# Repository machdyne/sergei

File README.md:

# Sergei Motherboard

Sergei is a motherboard that when paired with a [Sechzig](https://github.com/machdyne/sechzig) compute module can function as a computer.

This repo contains schematics, PCB layouts, pinouts, documentation and a 3D-printable case.

Find more information on the [Sergei product page](https://machdyne.com/product/sergei-motherboard/).

## Using Sergei

Sergei requires a Sechzig module to power on. **When inserting a Sechzig module, make sure that pin 2 on Sergei and pin 2 on the module are both on the same side.**

## Firmware

Sergei has a JTAG and USB CDC interface that are both accessible on the USB-C port. These interfaces are provided by a [fork of pico-dirtyJtag](https://github.com/machdyne/sergei/tree/main/firmware). You can update the RP2040 firmware by holding down the BOOT button and then applying power.

To build the firmware from source:

```
$ cd firmware/pico-dirtyJtag
$ mkdir build
$ cmake ..
$ make
```

## Programming

Program the configuration SRAM of a Sechzig module:

```
sudo openFPGALoader -c dirtyJtag image.bit
```

Program the configuration flash on a Sechzig MLx module:

```
sudo openFPGALoader -f -c dirtyJtag image.bit
```

Program the configuration flash on a Sechzig MX1 module:

```
sudo openFPGALoader -c dirtyJtag -f image.bit --fpga-part xc7a35tftg256
```

## Linux

See the [Kakao Linux](https://github.com/machdyne/kakao) repo for the latest instructions.

## Pinouts

### DDMI Port

See the [DDMI repo](https://github.com/machdyne/ddmi) for details.

## Revisions

| Revision | Stackup | Notes |
| -------- | ------- | ----- |
| V0 | JLC04161H-3313 | Initial production version |

## License

The contents of this repo are released under the [Lone Dynamics Open License](LICENSE.md) with the following exception(s):

  * The pico-dirtyJtag firmware is released under the MIT license; see the firmware LICENSE file for details.

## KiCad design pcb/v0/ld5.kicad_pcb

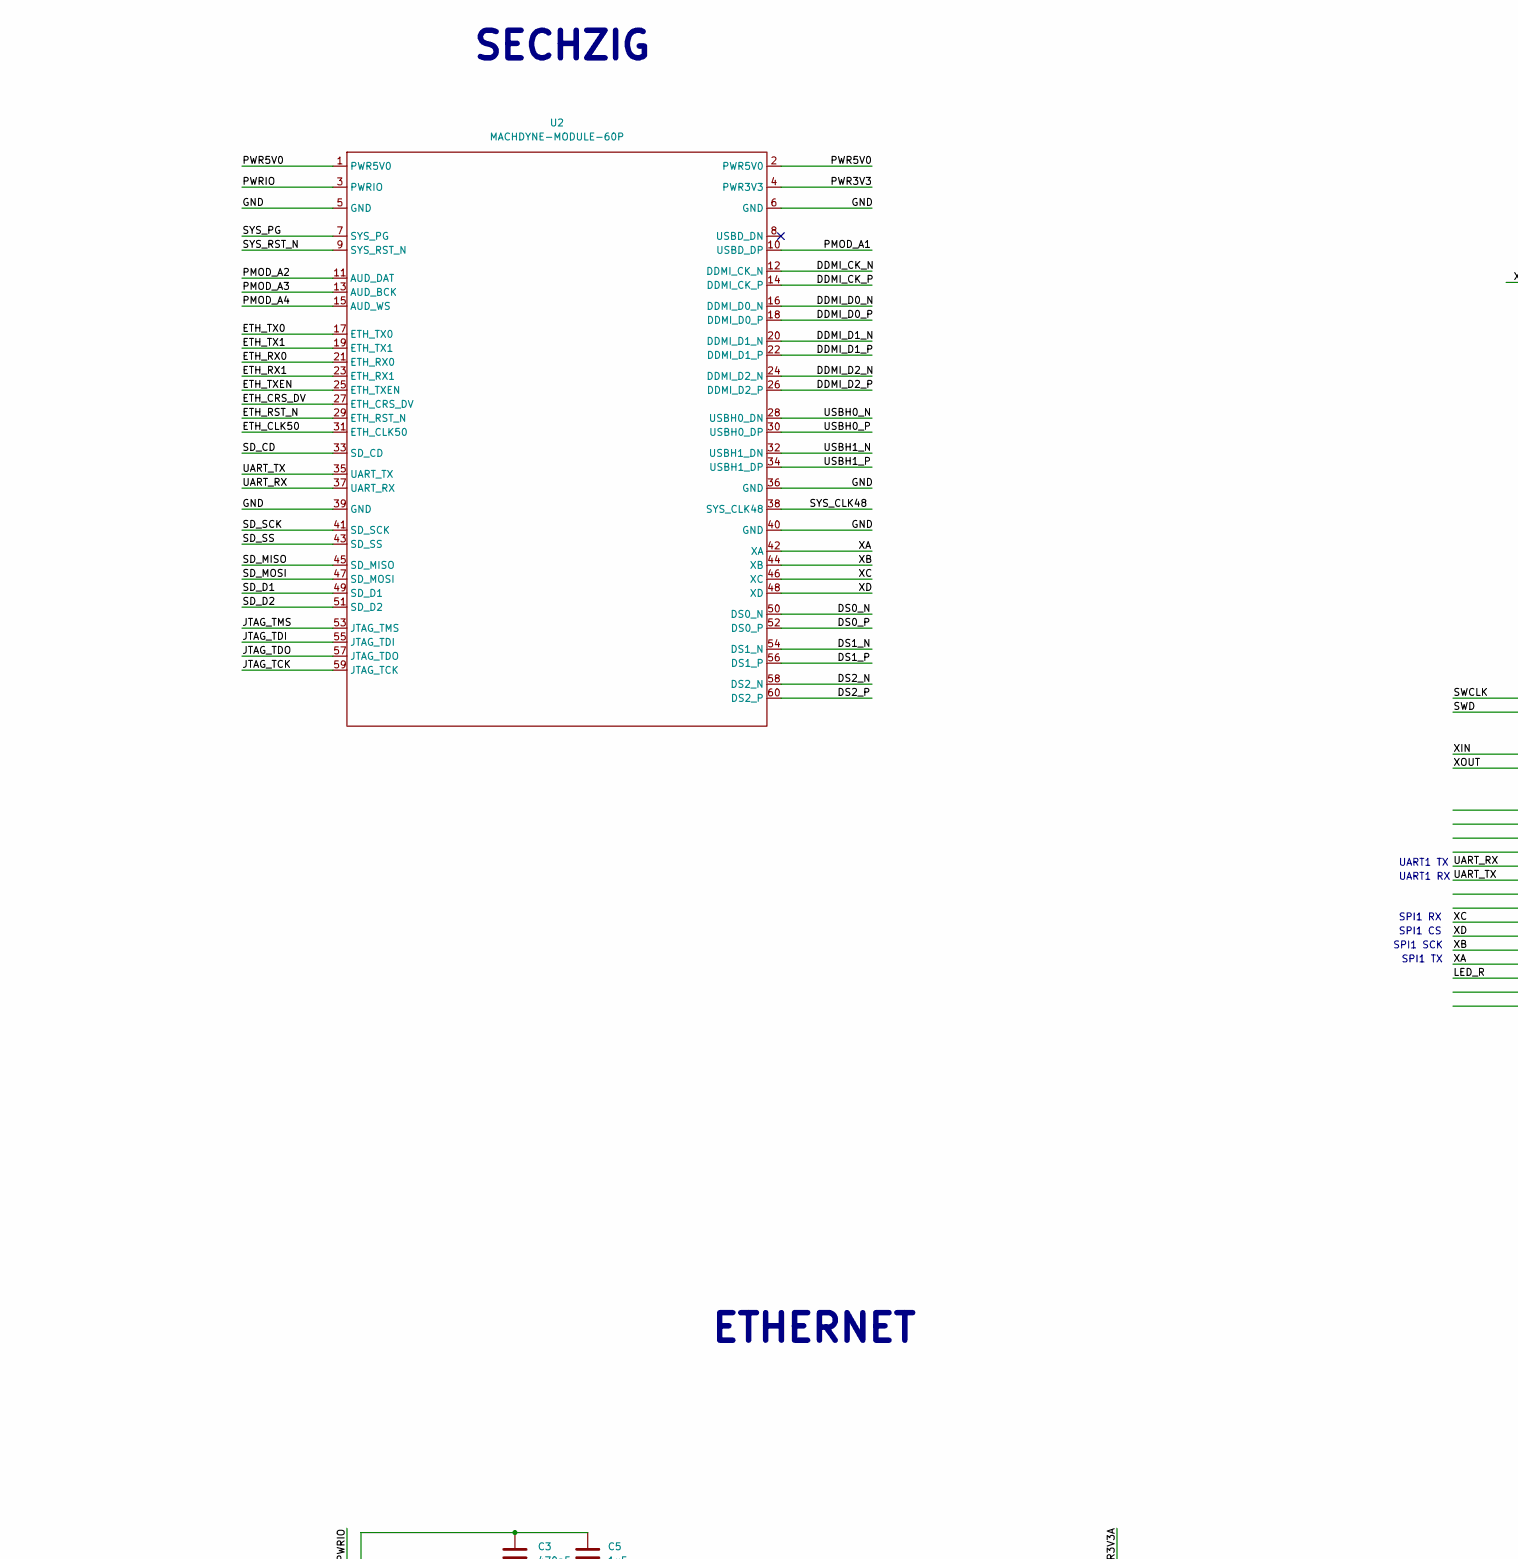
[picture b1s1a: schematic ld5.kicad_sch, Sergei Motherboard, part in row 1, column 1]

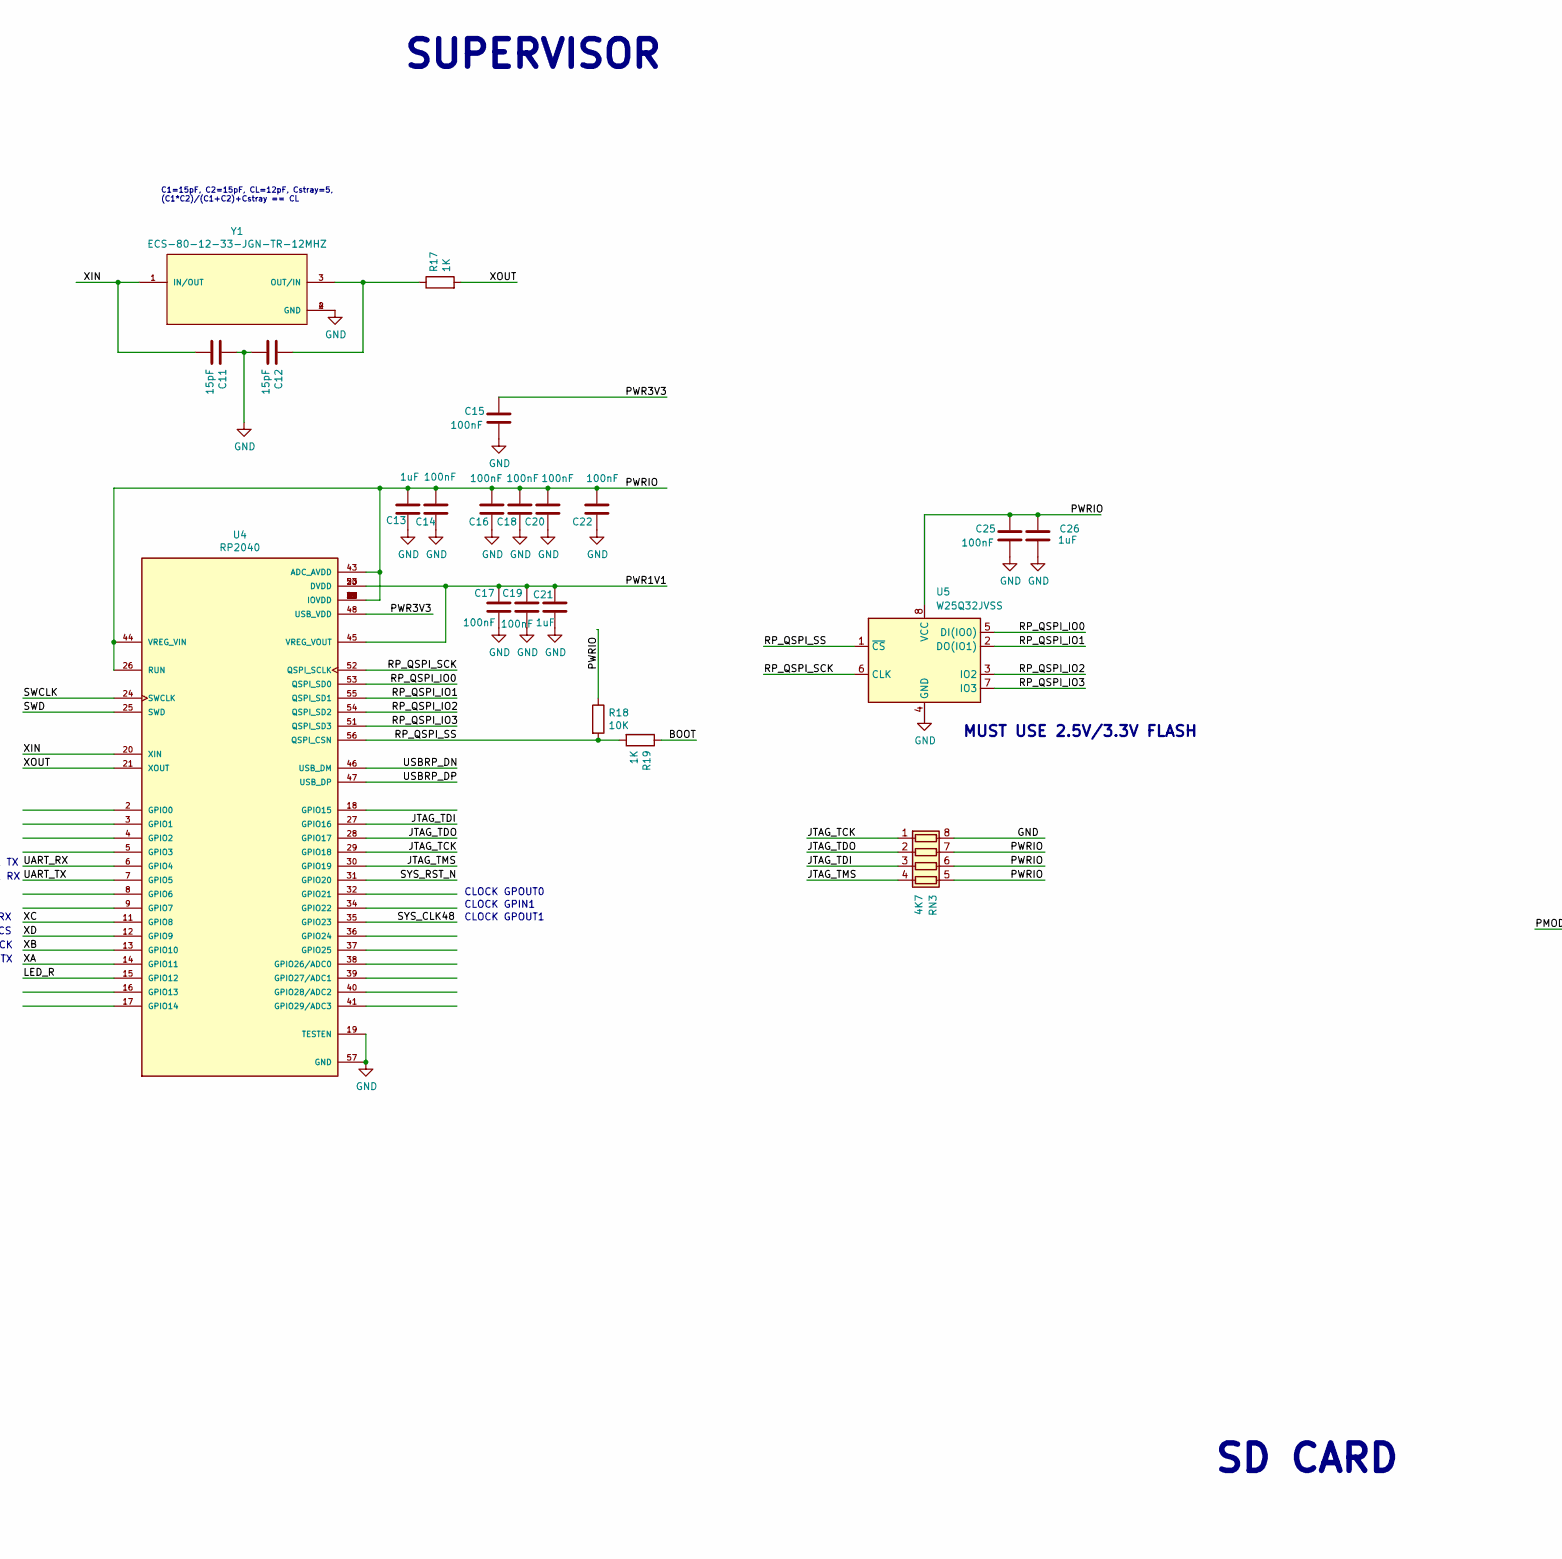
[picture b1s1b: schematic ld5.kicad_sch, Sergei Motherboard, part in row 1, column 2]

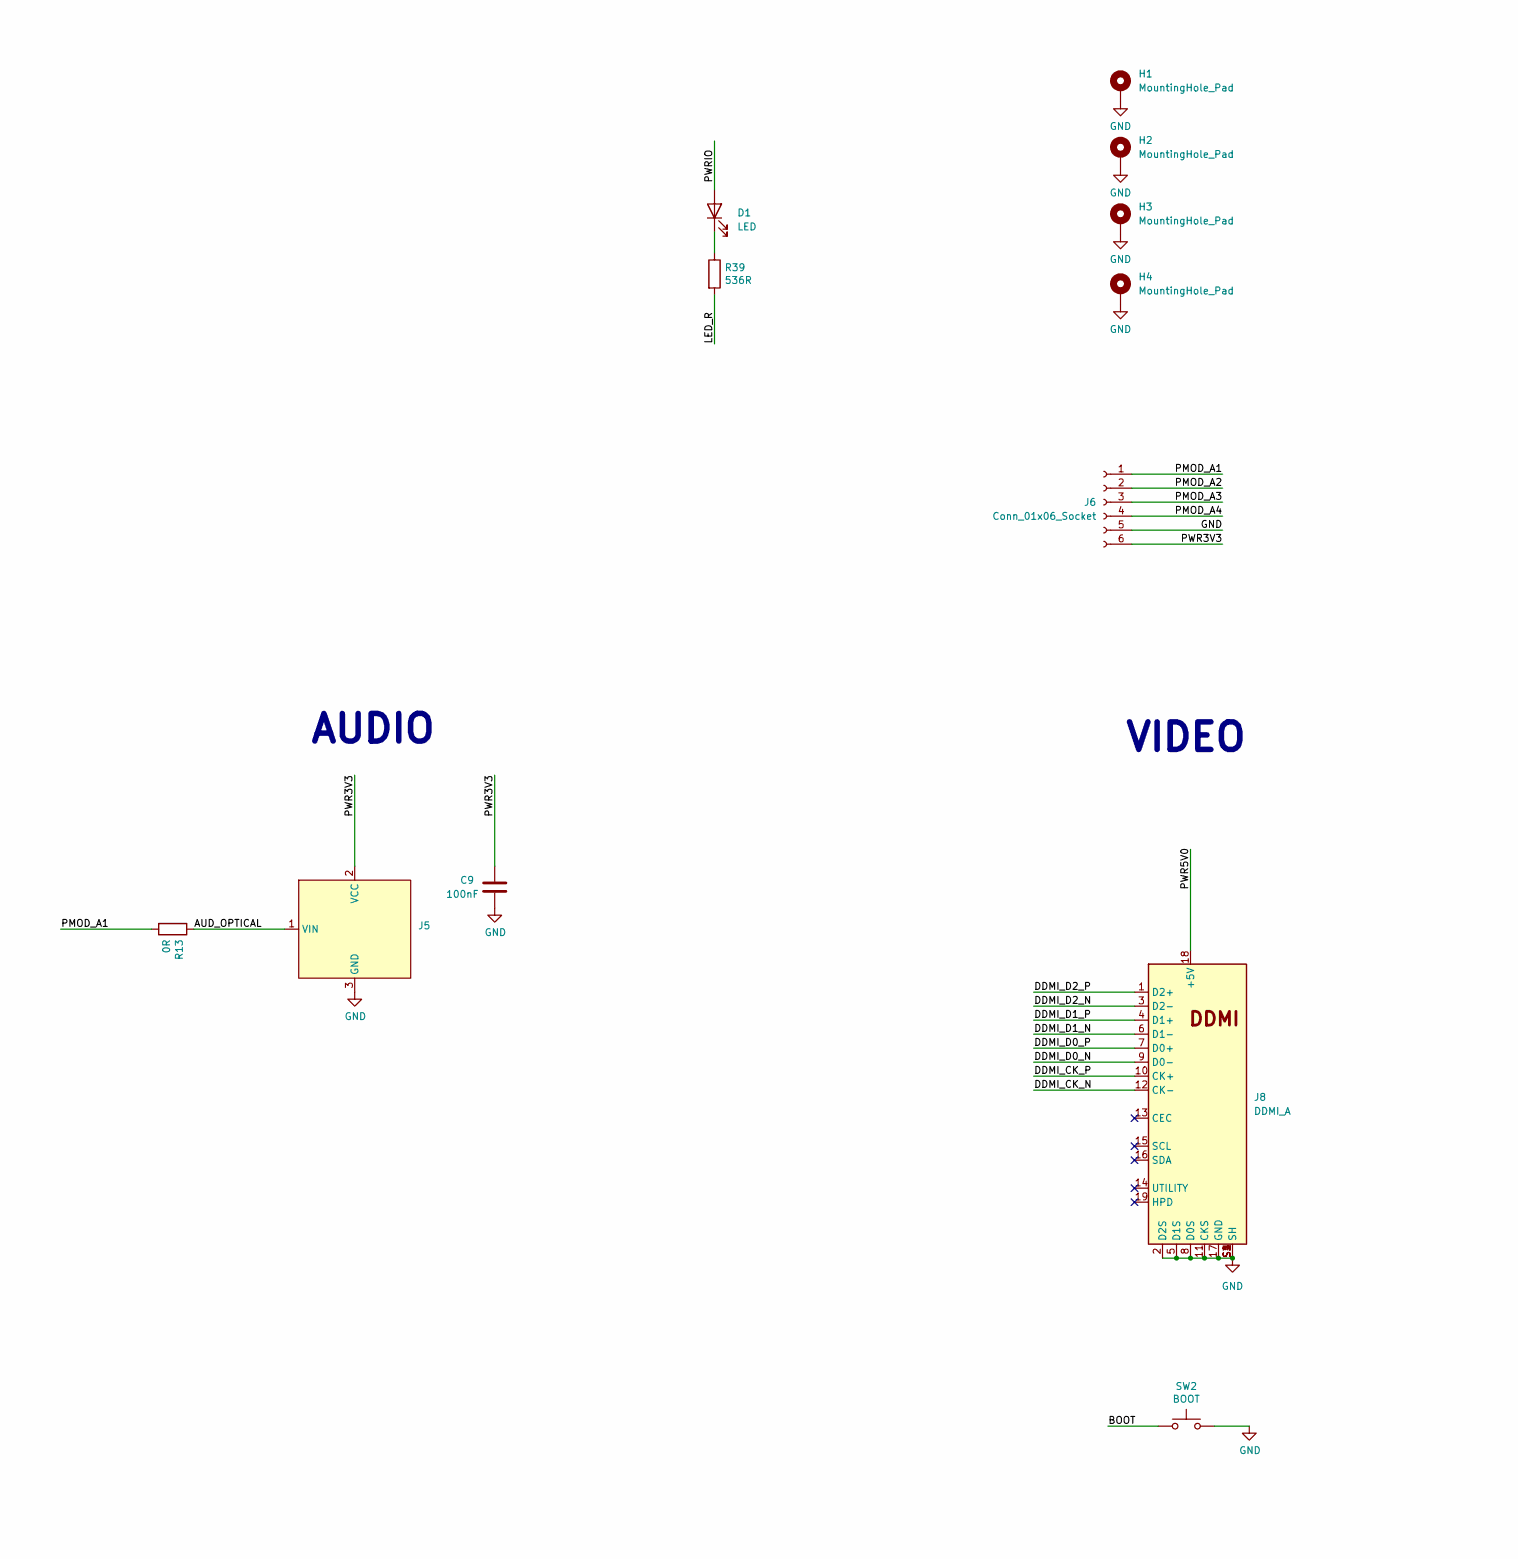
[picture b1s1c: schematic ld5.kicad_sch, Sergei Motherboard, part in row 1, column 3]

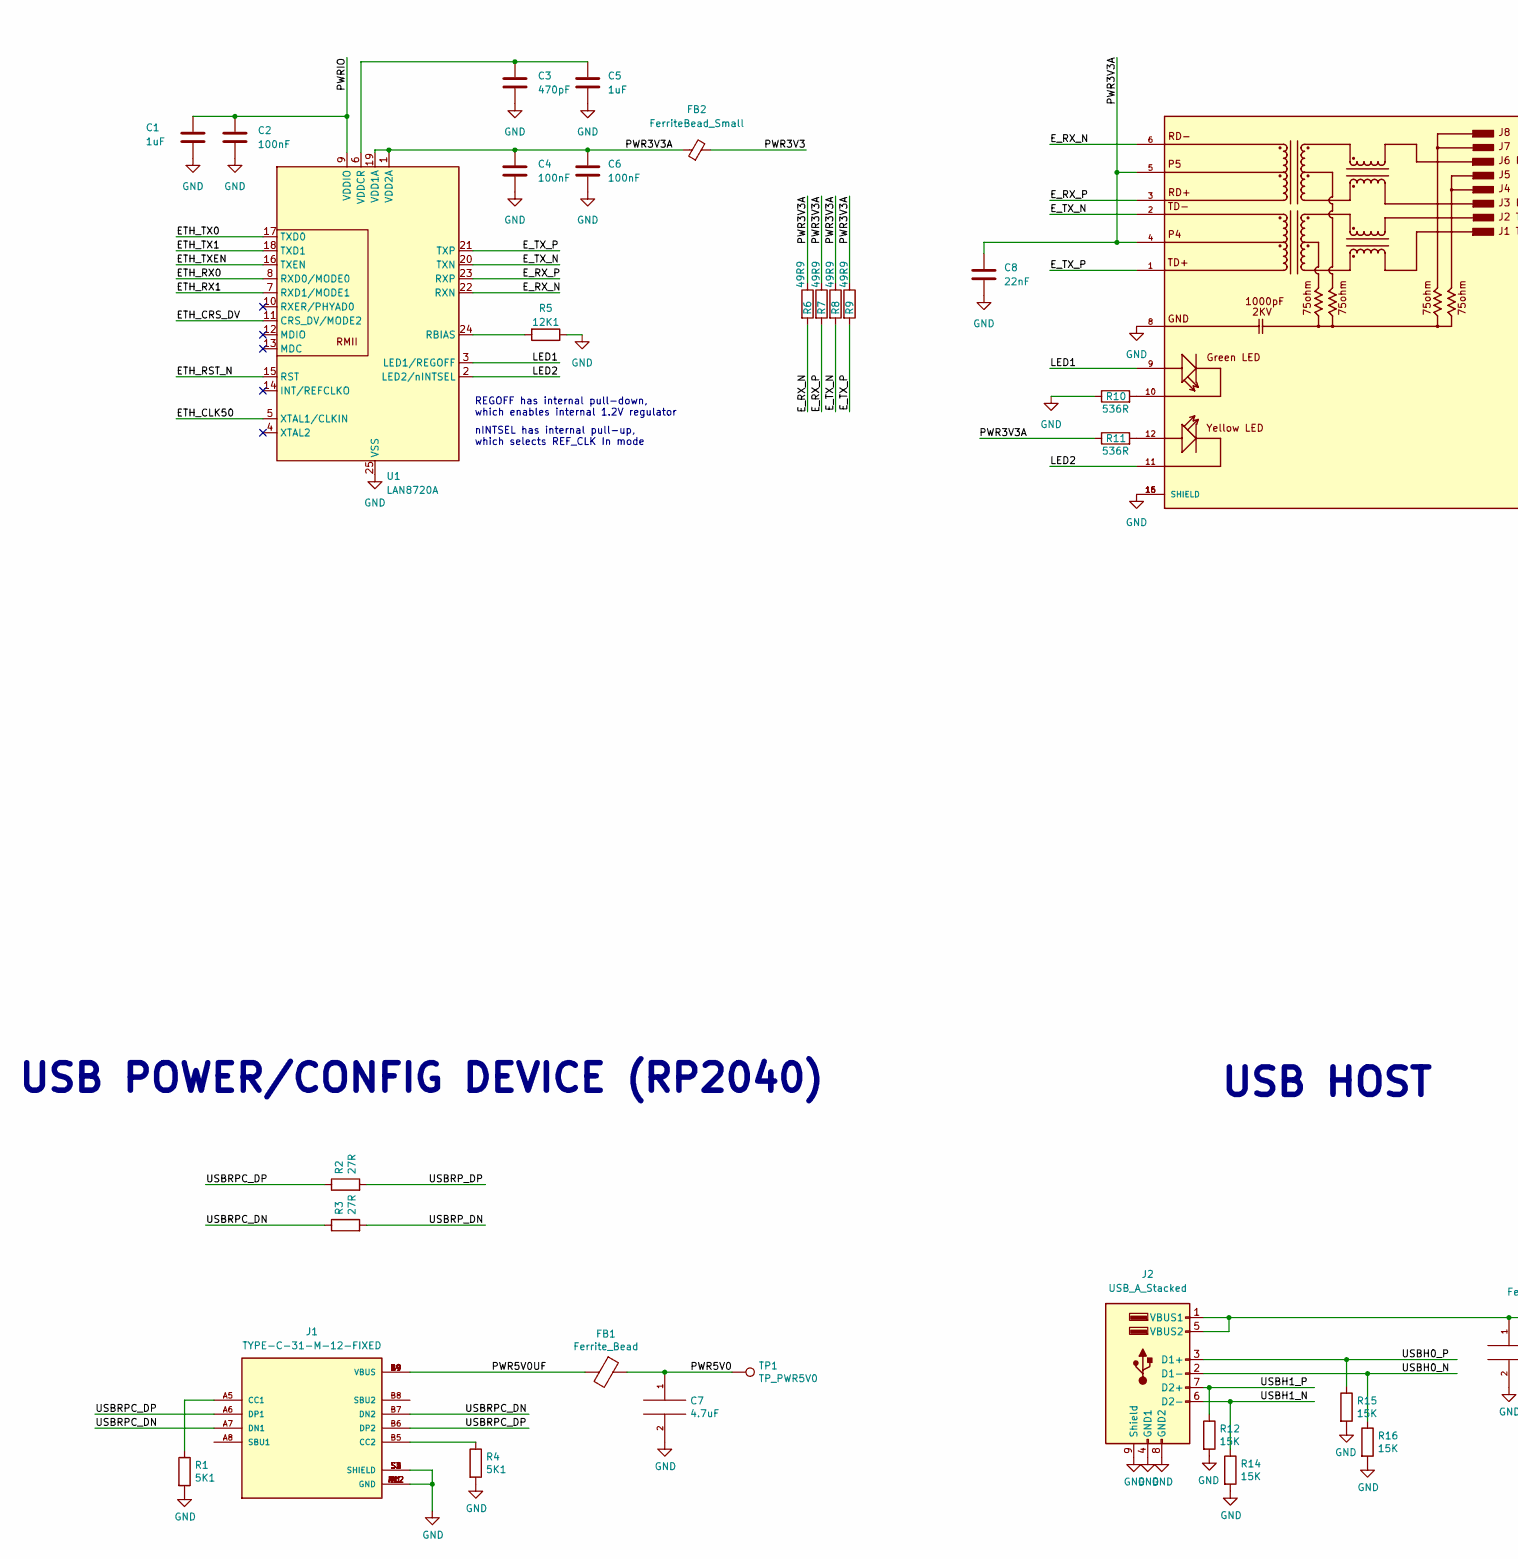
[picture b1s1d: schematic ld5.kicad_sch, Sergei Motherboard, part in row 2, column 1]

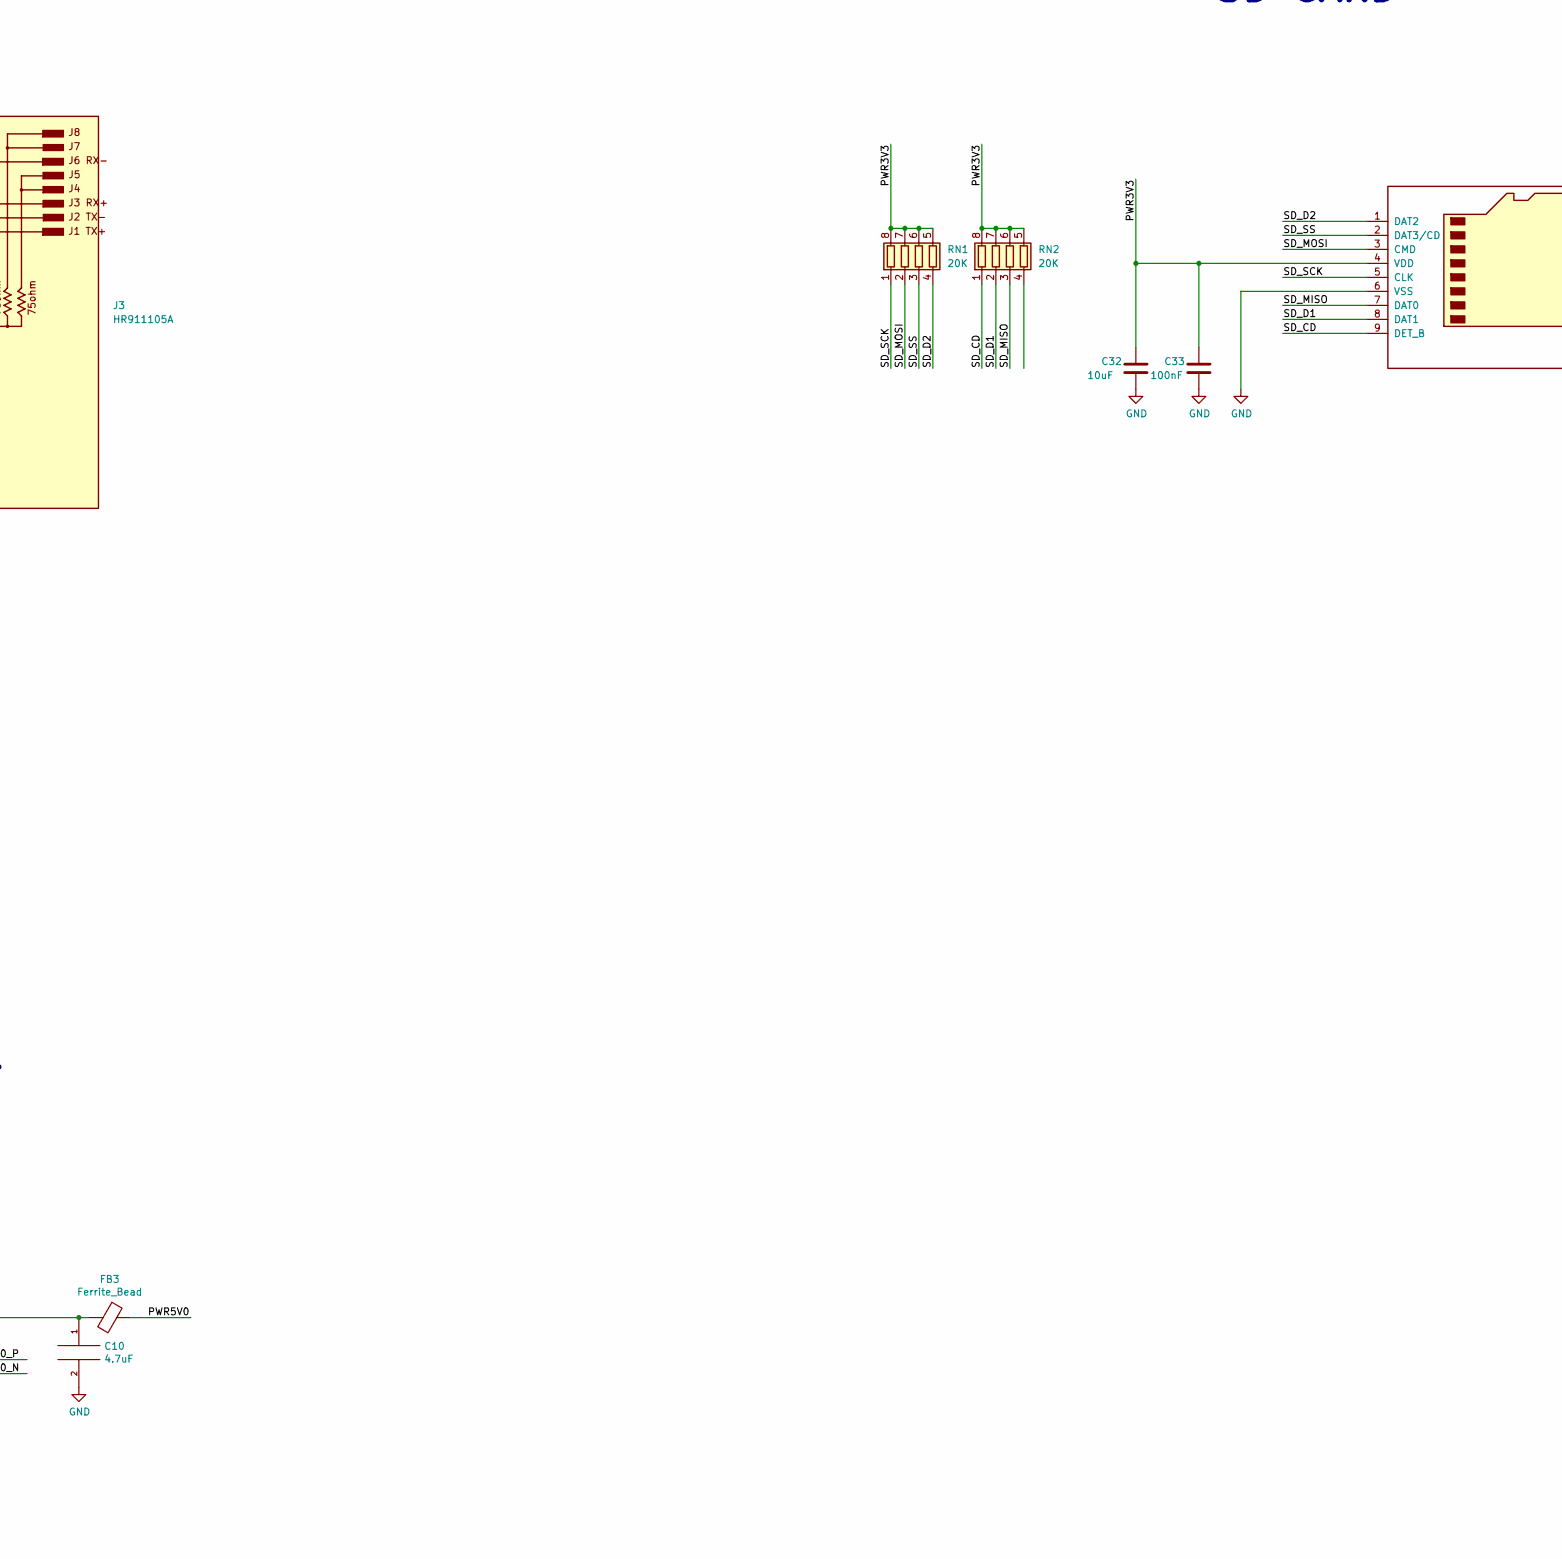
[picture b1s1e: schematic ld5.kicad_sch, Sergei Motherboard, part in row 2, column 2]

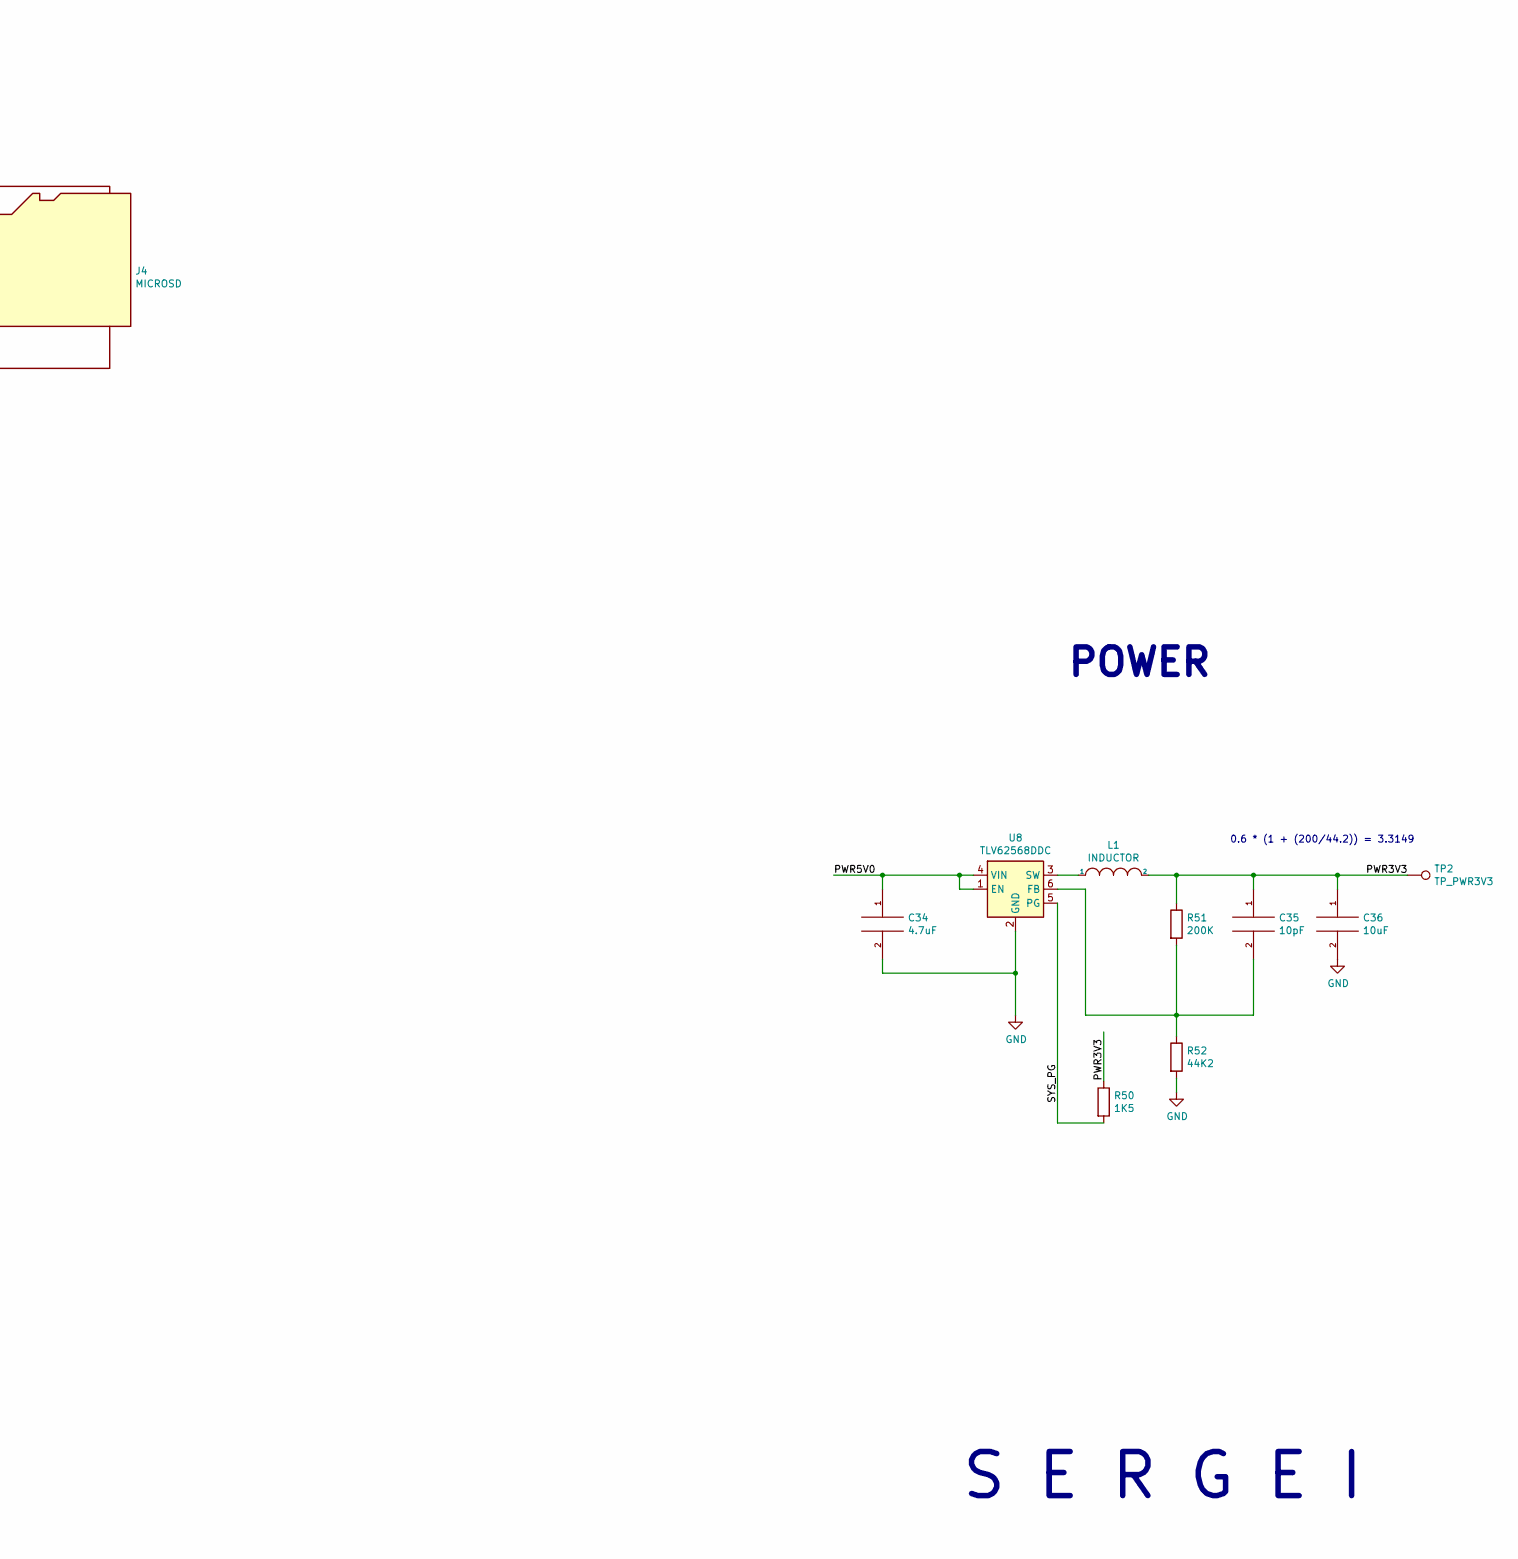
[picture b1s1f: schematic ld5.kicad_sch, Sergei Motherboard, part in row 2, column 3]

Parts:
C1, C5, C13, C21, C26: 1uF; C_0603_1608Metric
C2, C4, C6, C9, C14, C15, C16, C17, C18, C19, C20, C22, C25, C33: 100nF; C_0603_1608Metric
C3: 470pF; C_0603_1608Metric
C7, C10, C34: 4.7uF; C_0603_1608Metric
C8: 22nF; C_0603_1608Metric
C11, C12: 15pF; C_0603_1608Metric
C32, C36: 10uF; C_0603_1608Metric
C35: 10pF; C_0603_1608Metric
D1: LED; LED_1206_3216Metric
FB1, FB3: Ferrite_Bead; R_0603_1608Metric
FB2: FerriteBead_Small; R_0603_1608Metric
H1, H2, H3, H4: MountingHole_Pad; MountingHole_3.2mm_M3_Pad
J1: TYPE-C-31-M-12-FIXED; USB_C_Receptacle_HRO_TYPE-C-31-M-12-BIG-PADS; PARTREV A
J2: USB_A_Stacked; USB_A_Wuerth_61400826021_Horizontal_Stacked
J3: HR911105A; HANRUN_HR911105A; PARTREV A
J4: MICROSD; SDCARD
J5: ZGY133
J6: Conn_01x06_Socket; PinSocket_1x06_P2.54mm_Horizontal
J8: DDMI_A; HDMI_TE_1827059-3-FIXED
L1: INDUCTOR; L_0805_2012Metric
R1, R4: 5K1; R_0603_1608Metric
R2, R3: 27R; R_0603_1608Metric
R5: 12K1; R_0603_1608Metric
R6, R7, R8, R9: 49R9; R_0603_1608Metric
R10, R11, R39: 536R; R_0603_1608Metric
R12, R14, R15, R16: 15K; R_0603_1608Metric
R13: 0R; R_0603_1608Metric
R17, R19: 1K; R_0603_1608Metric
R18: 10K; R_0603_1608Metric
R50: 1K5; R_0603_1608Metric
R51: 200K; R_0603_1608Metric
R52: 44K2; R_0603_1608Metric
RN1, RN2: 20K; R_Array_Convex_4x0402
RN3: 4K7; R_Array_Convex_4x0402
SW2: BOOT; SW_Tactile_SPST_Angled_PTS645Vx39-2LFS
TP1: TP_PWR5V0; TestPoint_THTPad_D1.0mm_Drill0.5mm
TP2: TP_PWR3V3; TestPoint_THTPad_D1.0mm_Drill0.5mm
U1: LAN8720A; QFN-24-1EP_4x4mm_P0.5mm_EP2.6x2.6mm_ThermalVias
U2: MACHDYNE-MODULE-60P; MACHDYNE_EDGE_SOCKET_60P
U4: RP2040; RP2040-QFN-56-OFFICIAL; PARTREV 1.6.1
U5: W25Q32JVSS; SOIC-8_3.9x4.9mm_P1.27mm
U8: TLV62568DDC; SOT-23-6
Y1: ECS-80-12-33-JGN-TR-12MHZ; XTAL_ECS-240-8-33-AGN-TR

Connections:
/AUD_OPTICAL: J5.1 (VIN), R13.1
/BOOT: R19.1, SW2.1
/DDMI_CK_N: J8.12 (CK-), U2.12 (DDMI_CK_N)
/DDMI_CK_P: J8.10 (CK+), U2.14 (DDMI_CK_P)
/DDMI_D0_N: J8.9 (D0-), U2.16 (DDMI_D0_N)
/DDMI_D0_P: J8.7 (D0+), U2.18 (DDMI_D0_P)
/DDMI_D1_N: J8.6 (D1-), U2.20 (DDMI_D1_N)
/DDMI_D1_P: J8.4 (D1+), U2.22 (DDMI_D1_P)
/DDMI_D2_N: J8.3 (D2-), U2.24 (DDMI_D2_N)
/DDMI_D2_P: J8.1 (D2+), U2.26 (DDMI_D2_P)
/DS0_N: U2.50 (DS0_N)
/DS0_P: U2.52 (DS0_P)
/DS1_N: U2.54 (DS1_N)
/DS1_P: U2.56 (DS1_P)
/DS2_N: U2.58 (DS2_N)
/DS2_P: U2.60 (DS2_P)
/ETH_CLK50: U1.5 (XTAL1/CLKIN), U2.31 (ETH_CLK50)
/ETH_CRS_DV: U1.11 (CRS_DV/MODE2), U2.27 (ETH_CRS_DV)
/ETH_RST_N: U1.15 (RST), U2.29 (ETH_RST_N)
/ETH_RX0: U1.8 (RXD0/MODE0), U2.21 (ETH_RX0)
/ETH_RX1: U1.7 (RXD1/MODE1), U2.23 (ETH_RX1)
/ETH_TX0: U1.17 (TXD0), U2.17 (ETH_TX0)
/ETH_TX1: U1.18 (TXD1), U2.19 (ETH_TX1)
/ETH_TXEN: U1.16 (TXEN), U2.25 (ETH_TXEN)
/E_RX_N: J3.6, R6.2, U1.22 (RXN)
/E_RX_P: J3.3, R7.2, U1.23 (RXP)
/E_TX_N: J3.2, R8.2, U1.20 (TXN)
/E_TX_P: J3.1, R9.2, U1.21 (TXP)
/JTAG_TCK: RN3.1 (R1.1), U2.59 (JTAG_TCK), U4.29 (GPIO18)
/JTAG_TDI: RN3.3 (R3.1), U2.55 (JTAG_TDI), U4.27 (GPIO16)
/JTAG_TDO: RN3.2 (R2.1), U2.57 (JTAG_TDO), U4.28 (GPIO17)
/JTAG_TMS: RN3.4 (R4.1), U2.53 (JTAG_TMS), U4.30 (GPIO19)
/LED1: J3.9, U1.3 (LED1/REGOFF)
/LED2: J3.11, U1.2 (LED2/nINTSEL)
/LED_R: R39.2, U4.15 (GPIO12)
/PMOD_A1: J6.1, R13.2, U2.10 (USBD_DP)
/PMOD_A2: J6.2, U2.11 (AUD_DAT)
/PMOD_A3: J6.3, U2.13 (AUD_BCK)
/PMOD_A4: J6.4, U2.15 (AUD_WS)
/PWR1V1: C17.1, C19.1, C21.1, U4.23 (DVDD), U4.45 (VREG_VOUT), U4.50 (DVDD)
/PWR3V3: C9.1, C15.1, C32.1, C33.1, C35.1, C36.1, FB2.2, J4.4 (VDD), J5.2 (VCC), J6.6, L1.2, R50.1, R51.1, RN1.5 (R4.2), RN1.6 (R3.2), RN1.7 (R2.2), RN1.8 (R1.2), RN2.5 (R4.2), RN2.6 (R3.2), RN2.7 (R2.2), RN2.8 (R1.2), TP2.1, U2.4 (PWR3V3), U4.48 (USB_VDD)
/PWR3V3A: C4.1, C6.1, C8.1, FB2.1, J3.4, J3.5, R6.1, R7.1, R8.1, R9.1, R11.1, U1.1 (VDD2A), U1.19 (VDD1A)
/PWR5V0: C7.1, C34.1, FB1.1, FB3.1, J8.18 (+5V), TP1.1, U2.1 (PWR5V0), U2.2 (PWR5V0), U8.1 (EN), U8.4 (VIN)
/PWR5V0UF: FB1.2, J1.A4 (VBUS), J1.A9 (VBUS), J1.B4 (VBUS), J1.B9 (VBUS)
/PWRIO: C1.1, C2.1, C13.1, C14.1, C16.1, C18.1, C20.1, C22.1, C25.1, C26.1, D1.2 (A), R18.1, RN3.5 (R4.2), RN3.6 (R3.2), RN3.7 (R2.2), U1.9 (VDDIO), U2.3 (PWRIO), U4.1 (IOVDD), U4.10 (IOVDD), U4.22 (IOVDD), U4.26 (RUN), U4.33 (IOVDD), U4.42 (IOVDD), U4.43 (ADC_AVDD), U4.44 (VREG_VIN), U4.49 (IOVDD), U5.8 (VCC)
/RP_QSPI_IO0: U4.53 (QSPI_SD0), U5.5 (DI(IO0))
/RP_QSPI_IO1: U4.55 (QSPI_SD1), U5.2 (DO(IO1))
/RP_QSPI_IO2: U4.54 (QSPI_SD2), U5.3 (IO2)
/RP_QSPI_IO3: U4.51 (QSPI_SD3), U5.7 (IO3)
/RP_QSPI_SCK: U4.52 (QSPI_SCLK), U5.6 (CLK)
/RP_QSPI_SS: R18.2, R19.2, U4.56 (QSPI_CSN), U5.1 (~CS)
/SD_CD: J4.9 (DET_B), RN2.1 (R1.1), U2.33 (SD_CD)
/SD_D1: J4.8 (DAT1), RN2.2 (R2.1), U2.49 (SD_D1)
/SD_D2: J4.1 (DAT2), RN1.4 (R4.1), U2.51 (SD_D2)
/SD_MISO: J4.7 (DAT0), RN2.3 (R3.1), U2.45 (SD_MISO)
/SD_MOSI: J4.3 (CMD), RN1.2 (R2.1), U2.47 (SD_MOSI)
/SD_SCK: J4.5 (CLK), RN1.1 (R1.1), U2.41 (SD_SCK)
/SD_SS: J4.2 (DAT3/CD), RN1.3 (R3.1), U2.43 (SD_SS)
/SWCLK: U4.24 (SWCLK)
/SWD: U4.25 (SWD)
/SYS_CLK48: U2.38 (SYS_CLK48), U4.35 (GPIO23)
/SYS_PG: R50.2, U2.7 (SYS_PG), U8.5 (PG)
/SYS_RST_N: U2.9 (SYS_RST_N), U4.31 (GPIO20)
/UART_RX: U2.37 (UART_RX), U4.6 (GPIO4)
/UART_TX: U2.35 (UART_TX), U4.7 (GPIO5)
/USBH0_N: J2.2 (D1-), R16.1, U2.28 (USBH0_DN)
/USBH0_P: J2.3 (D1+), R15.1, U2.30 (USBH0_DP)
/USBH1_N: J2.6 (D2-), R14.1, U2.32 (USBH1_DN)
/USBH1_P: J2.7 (D2+), R12.1, U2.34 (USBH1_DP)
/USBRPC_DN: J1.A7 (DN1), J1.B7 (DN2), R3.1
/USBRPC_DP: J1.A6 (DP1), J1.B6 (DP2), R2.1
/USBRP_DN: R3.2, U4.46 (USB_DM)
/USBRP_DP: R2.2, U4.47 (USB_DP)
/XA: U2.42 (XA), U4.14 (GPIO11)
/XB: U2.44 (XB), U4.13 (GPIO10)
/XC: U2.46 (XC), U4.11 (GPIO8)
/XD: U2.48 (XD), U4.12 (GPIO9)
/XIN: C11.2, U4.20 (XIN), Y1.1 (IN/OUT)
/XOUT: R17.2, U4.21 (XOUT)
GND: C1.2, C2.2, C3.2, C4.2, C5.2, C6.2, C7.2, C8.2, C9.2, C10.2, C11.1, C12.2, C13.2, C14.2, C15.2, C16.2, C17.2, C18.2, C19.2, C20.2, C21.2, C22.2, C25.2, C26.2, C32.2, C33.2, C34.2, C36.2, H1.1, H2.1, H3.1, H4.1, J1.A1 (GND), J1.A12 (GND), J1.B1 (GND), J1.B12 (GND), J1.S1 (SHIELD), J1.S2 (SHIELD), J1.S3 (SHIELD), J1.S4 (SHIELD), J2.4 (GND1), J2.8 (GND2), J2.9 (Shield), J3.8, J3.15 (SHIELD), J3.16 (SHIELD), J4.6 (VSS), J5.3 (GND), J6.5, J8.2 (D2S), J8.5 (D1S), J8.8 (D0S), J8.11 (CKS), J8.17 (GND), J8.S1 (SH), J8.S2 (SH), J8.S3 (SH), J8.S4 (SH), R1.2, R4.2, R5.1, R10.1, R12.2, R14.2, R15.2, R16.2, R52.2, RN3.8 (R1.2), SW2.2, U1.25 (VSS), U2.5 (GND), U2.6 (GND), U2.36 (GND), U2.39 (GND), U2.40 (GND), U4.19 (TESTEN), U4.57 (GND), U5.4 (GND), U8.2 (GND), Y1.2 (GND), Y1.4 (GND)
unnamed: D1.1 (K), R39.1
unnamed: J1.A5 (CC1), R1.1
unnamed: J1.B5 (CC2), R4.1
unnamed: C10.1, FB3.2, J2.1 (VBUS1), J2.5 (VBUS2)
unnamed: J3.10, R10.2
unnamed: J3.12, R11.2
unnamed: R5.2, U1.24 (RBIAS)
unnamed: C3.1, C5.1, U1.6 (VDDCR)
unnamed: C35.2, R51.2, R52.1, U8.6 (FB)
unnamed: L1.1, U8.3 (SW)
unnamed: C12.1, R17.1, Y1.3 (OUT/IN)

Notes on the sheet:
CLOCK GPOUT1
S E R G E I
nINTSEL has internal pull-up, which selects REF_CLK In mode
0.6 * (1 + (200/44.2)) = 3.3149
SD CARD
SPI1 CS
MUST USE 2.5V/3.3V FLASH
C1=15pF, C2=15pF, CL=12pF, Cstray=5, (C1*C2)/(C1+C2)+Cstray == CL
UART1 TX
REGOFF has internal pull-down, which enables internal 1.2V regulator
POWER
SECHZIG
SPI1 RX
SPI1 TX
VIDEO
CLOCK GPIN1
USB POWER/CONFIG DEVICE (RP2040)
CLOCK GPOUT0
SUPERVISOR
AUDIO
USB HOST
SPI1 SCK
ETHERNET
UART1 RX

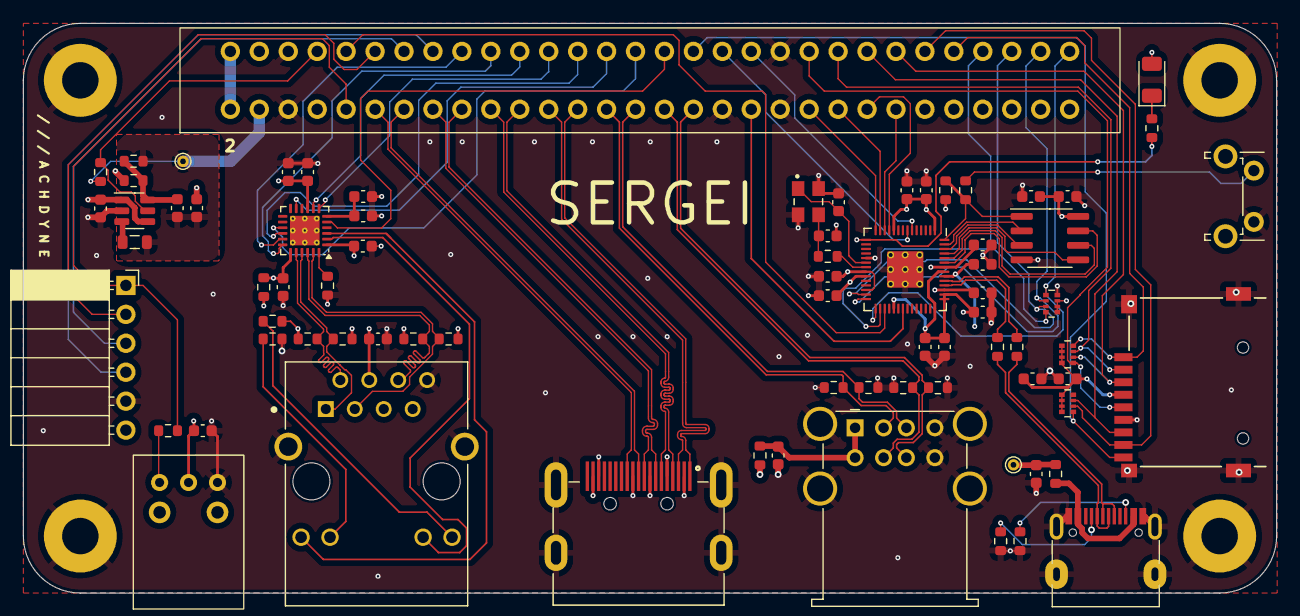
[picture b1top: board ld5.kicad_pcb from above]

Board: 4 copper layers, 110.0 x 50.0 mm, 80 parts (0 on the bottom side), 83 nets.

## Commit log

2024-10-18 adjust case
2024-12-11 add dual core spi mode bitstreams
2024-12-23 add mx2 bitstreams

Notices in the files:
pcb/v0/ld5.kicad_sch:
Copyright © 2024 Lone Dynamics Corporation
